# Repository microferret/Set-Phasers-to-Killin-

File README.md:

Within the world of electric instruments (particularly that of the electric guitar and bass), there are a wealth of ways to modify your instrument's sound. This is typically done via the use of foot-controlled effects pedals. One type of effect pedal, the "Phaser" pedal, shifts the phase of the output signal sent to a instrument amplifier. This creates a distinct sound that can be very desirable in certain applications. This type of effect pedal is what I have created a custom design for. My pedal will essentially resemble a MXR Phase 45 pedal in terms of architecture but will also have a togglable extra phase shifting network to shift the phase of the output by an extra amount.

Below is a screenshot of the schematic for my project:

Below is a screenshot of the PCB layout:

Below are screenshots of the a 3D render of the PCB:

See included Obsidian file for design process documentation.
I have an explaination of how the device works in the documentation as well. Below is the source I used to help me with this project:
https://barbarach.com/breadboard-a-simple-phaser/

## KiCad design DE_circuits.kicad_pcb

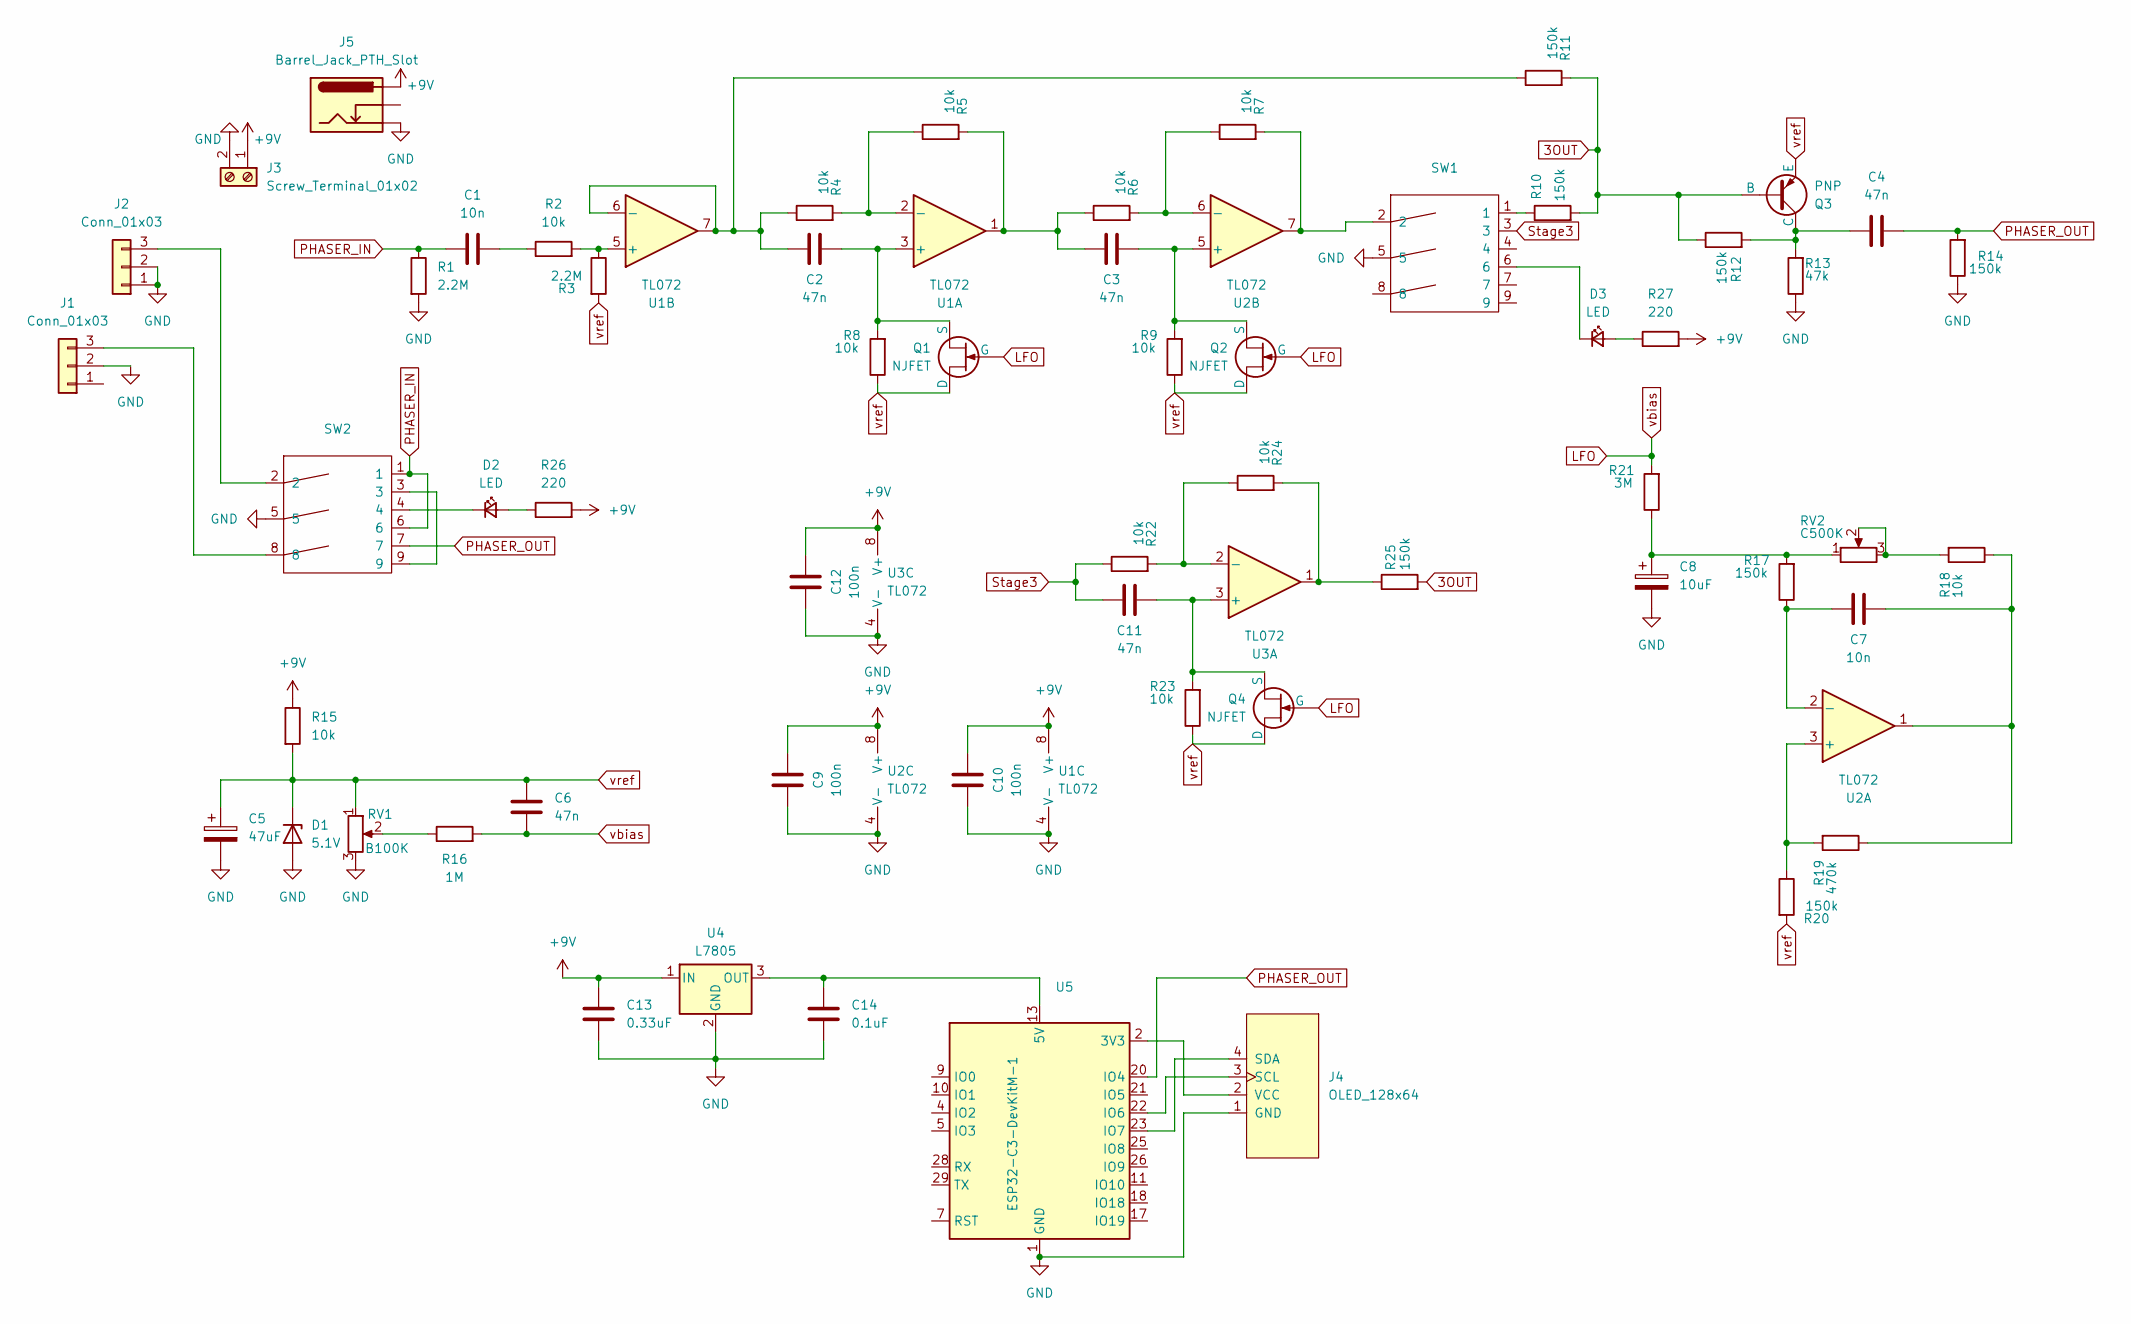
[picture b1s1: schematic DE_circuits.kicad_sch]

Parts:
C1, C7: 10n; C_Disc_D5.0mm_W2.5mm_P2.50mm
C2, C3, C4, C6, C11: 47n; C_Disc_D5.0mm_W2.5mm_P2.50mm
C5: 47uF; CP_Radial_D4.0mm_P1.50mm
C8: 10uF; CP_Radial_D4.0mm_P1.50mm
C9, C10, C12: 100n; C_Disc_D5.0mm_W2.5mm_P2.50mm
C13: 0.33uF; C_Disc_D5.0mm_W2.5mm_P2.50mm
C14: 0.1uF; C_Disc_D5.0mm_W2.5mm_P2.50mm
D1: 5.1V; D_MELF-RM10_Universal_Handsoldering
D2, D3: LED; LED_D1.8mm_W1.8mm_H2.4mm_Horizontal_O1.27mm_Z1.6mm
J1, J2: Conn_01x03; 1x03_P2.54mm
J3: Screw_Terminal_01x02; ScrewTerminal_1x02_P3.5mm_Horizontal_Black
J4: OLED_128x64
J5: Barrel_Jack_PTH_Slot
Q1, Q2, Q4: NJFET; TO-92L_HandSolder
Q3: PNP; TO-92L_HandSolder
R1, R3: 2.2M; R_Axial_DIN0204_L3.6mm_D1.6mm_P1.90mm_Vertical
R2, R4, R5, R6, R7, R8, R9, R15, R18, R22, R23, R24: 10k; R_Axial_DIN0204_L3.6mm_D1.6mm_P1.90mm_Vertical
R10, R11, R12, R14, R17, R20, R25: 150k; R_Axial_DIN0204_L3.6mm_D1.6mm_P1.90mm_Vertical
R13: 47k; R_Axial_DIN0204_L3.6mm_D1.6mm_P1.90mm_Vertical
R16: 1M; R_Axial_DIN0204_L3.6mm_D1.6mm_P1.90mm_Vertical
R19: 470k; R_Axial_DIN0204_L3.6mm_D1.6mm_P1.90mm_Vertical
R21: 3M; R_Axial_DIN0204_L3.6mm_D1.6mm_P1.90mm_Vertical
R26, R27: 220; R_Axial_DIN0204_L3.6mm_D1.6mm_P1.90mm_Vertical
RV1: B100K; Potentiometer_ACP_CA6-H2,5_Horizontal
RV2: C500K; Potentiometer_ACP_CA6-H2,5_Horizontal
SW1, SW2: Switch-3PDT
U1, U2, U3: TL072; DIP-8_W7.62mm
U4: L7805; TO-220-3_Vertical
U5: ESP32-C3-DevKitM-1

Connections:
3OUT: Q3.2 (B), R10.2, R11.2, R12.1, R25.2
+9V: C9.2, C10.2, C12.2, C13.2, J3.1, J5.PWR, R15.1, R26.2, R27.2, U1.8 (V+), U2.8 (V+), U3.8 (V+), U4.1 (IN)
GND: C5.2, C8.2, C9.1, C10.1, C12.1, C13.1, C14.1, D1.2 (A), J1.2, J2.1, J2.2, J3.2, J4.1 (GND), J5.GND, R1.2, R13.1, R14.1, RV1.3, SW1.5, SW2.5, U1.4 (V-), U2.4 (V-), U3.4 (V-), U4.2 (GND), U5.1 (GND), U5.6 (GND), U5.8 (GND), U5.12 (GND), U5.15 (GND), U5.16 (GND), U5.19 (GND), U5.24 (GND), U5.27 (GND), U5.30 (GND)
LFO: C6.1, Q1.2 (G), Q2.2 (G), Q4.2 (G), R16.2, R21.2
unnamed: C1.2, R2.1
unnamed: C3.1, R5.2, R6.1, U1.1
unnamed: C7.2, R18.1, R19.1, U2.1
unnamed: C8.1, R17.2, R21.1, RV2.1
unnamed: D2.2 (A), R26.1
unnamed: D2.1 (K), SW2.4
unnamed: D3.2 (A), R27.1
unnamed: D3.1 (K), SW1.6
unnamed: J1.3, SW2.8
unnamed: J2.3, SW2.2
unnamed: J4.3 (SCL), U5.22 (IO6)
unnamed: J4.4 (SDA), U5.23 (IO7)
unnamed: J4.2 (VCC), U5.2 (3V3), U5.3 (3V3)
unnamed: C2.2, Q1.3 (S), R8.2, U1.3 (+)
unnamed: C3.2, Q2.3 (S), R9.2, U2.5 (+)
unnamed: C4.1, Q3.1 (C), R12.2, R13.2
unnamed: C11.2, Q4.3 (S), R23.2, U3.3 (+)
unnamed: R7.2, SW1.2, U2.7
unnamed: R10.1, SW1.1
unnamed: R16.1, RV1.2
unnamed: R18.2, RV2.2, RV2.3
unnamed: R24.2, R25.1, U3.1
unnamed: SW2.3, SW2.9
unnamed: R4.2, R5.1, U1.2 (-)
unnamed: R2.2, R3.1, U1.5 (+)
unnamed: C2.1, R4.1, R11.1, U1.6 (-), U1.7
unnamed: R19.2, R20.1, U2.3 (+)
unnamed: C7.1, R17.1, U2.2 (-)
unnamed: R6.2, R7.1, U2.6 (-)
unnamed: R22.2, R24.1, U3.2 (-)
unnamed: C14.2, U4.3 (OUT), U5.13 (5V), U5.14 (5V)
PHASER_IN: C1.1, R1.1, SW2.1, SW2.6
PHASER_OUT: C4.2, R14.2, SW2.7, U5.20 (IO4)
Stage3: C11.1, R22.1, SW1.3
vref: C5.1, C6.2, D1.1 (K), Q1.1 (D), Q2.1 (D), Q3.3 (E), Q4.1 (D), R3.2, R8.1, R9.1, R15.2, R20.2, R23.1, RV1.1

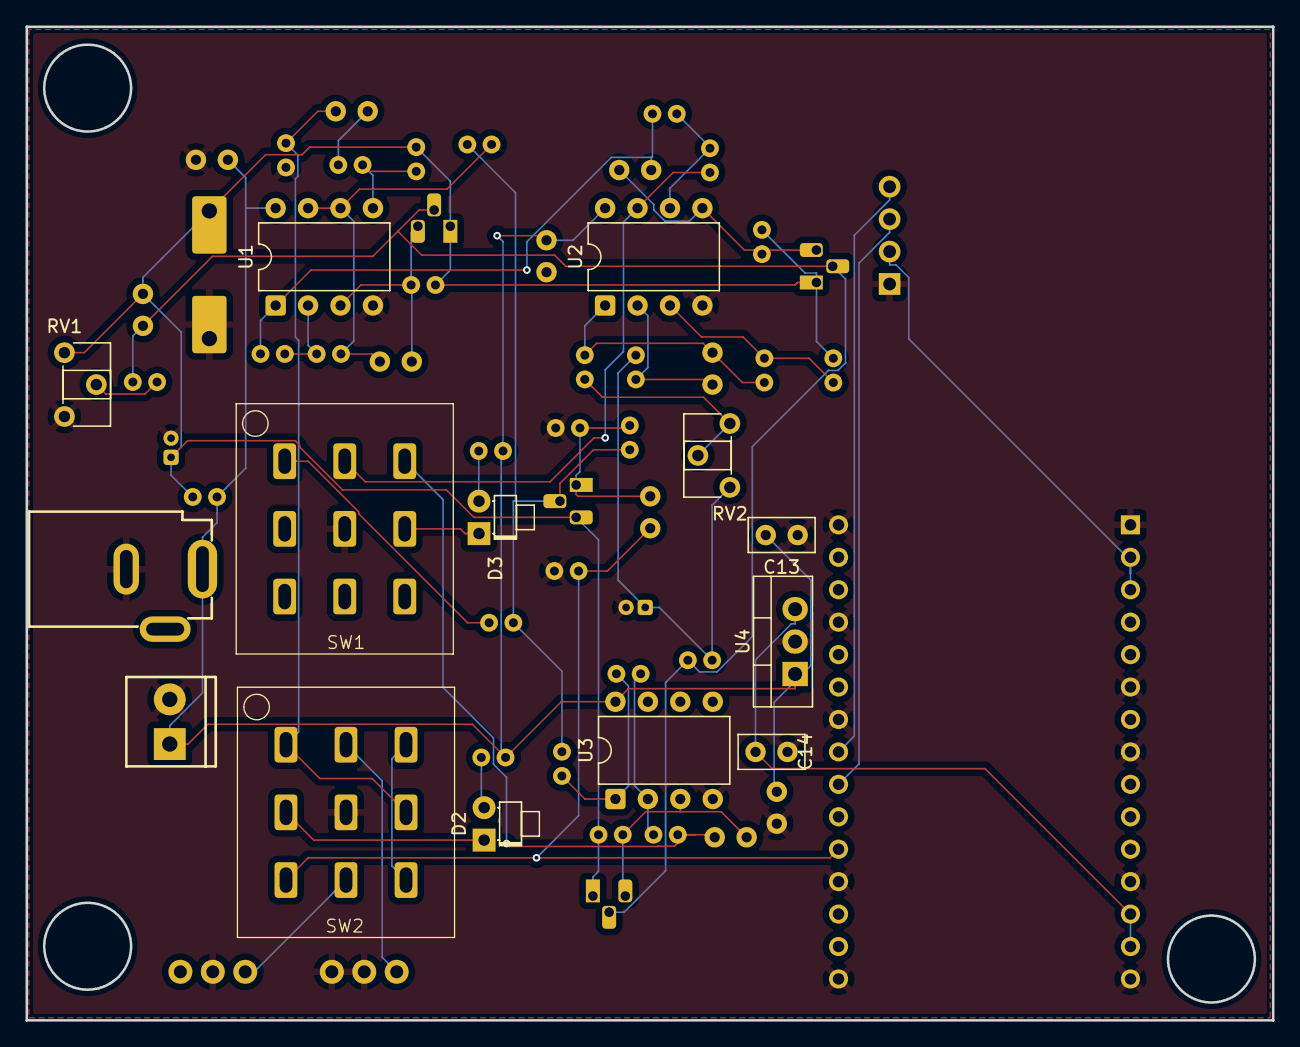
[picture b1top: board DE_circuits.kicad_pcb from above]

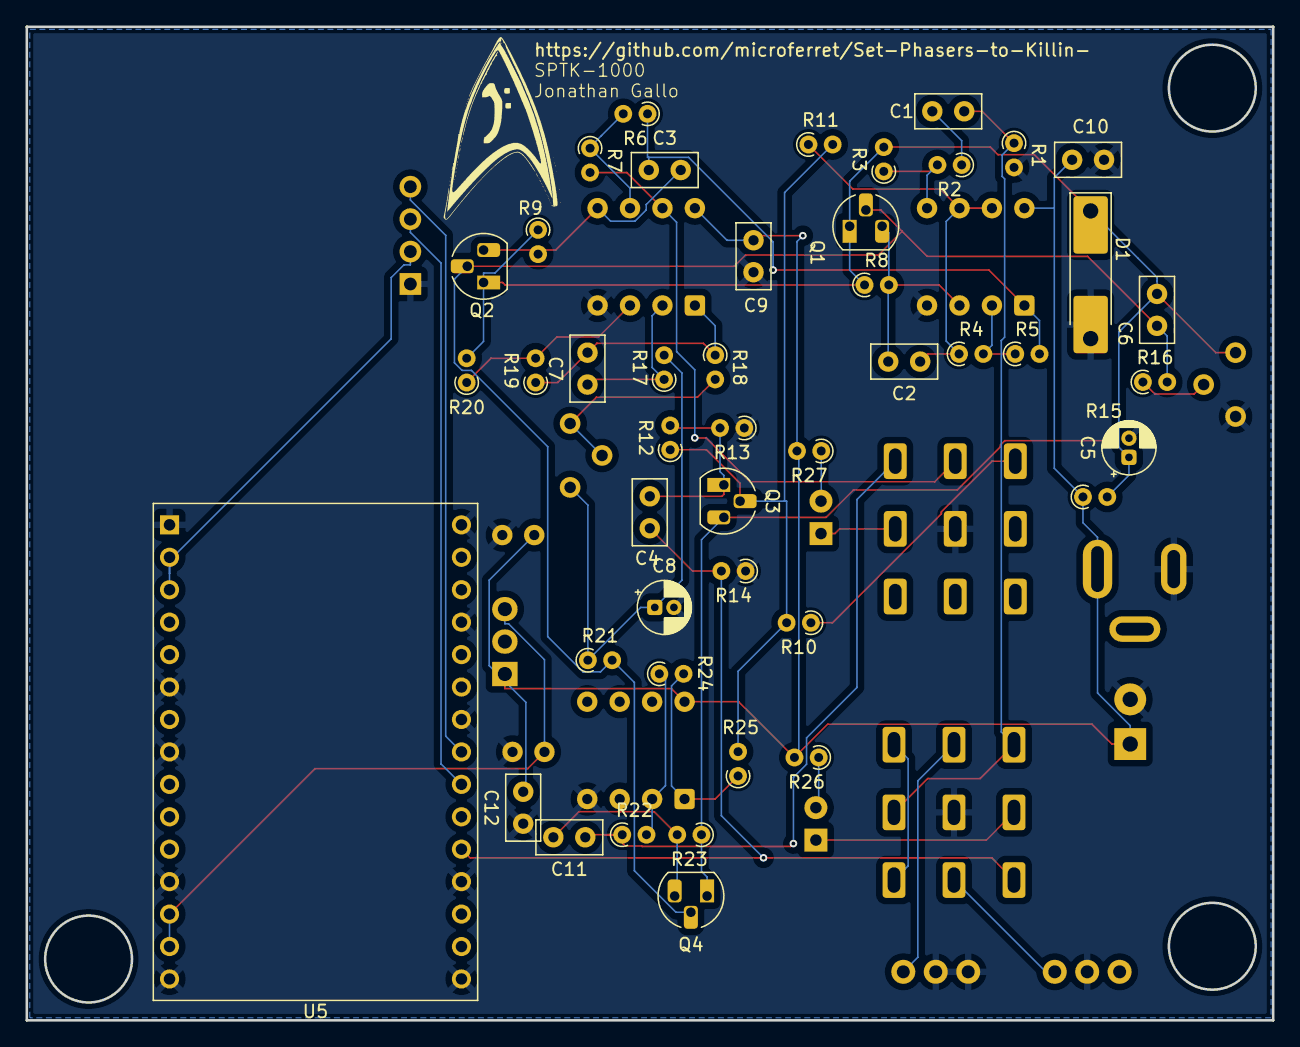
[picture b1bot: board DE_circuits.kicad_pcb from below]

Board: 2 copper layers, 97.6 x 77.8 mm, 62 parts (45 on the bottom side), 39 nets.

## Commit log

2025-12-24 Add files via upload
    KiCAD Files
2025-12-24 Add files via upload
    Obsidian files (documentation)
2025-12-26 Phaser Fusion Assembly
    Fusion files for the Phaser enclosure
2026-02-16 Final Update of PCB
    This is the last iteration of my project unless there is a real serious issue that needs to be rectified.
2026-02-16 New Obsidian Files
